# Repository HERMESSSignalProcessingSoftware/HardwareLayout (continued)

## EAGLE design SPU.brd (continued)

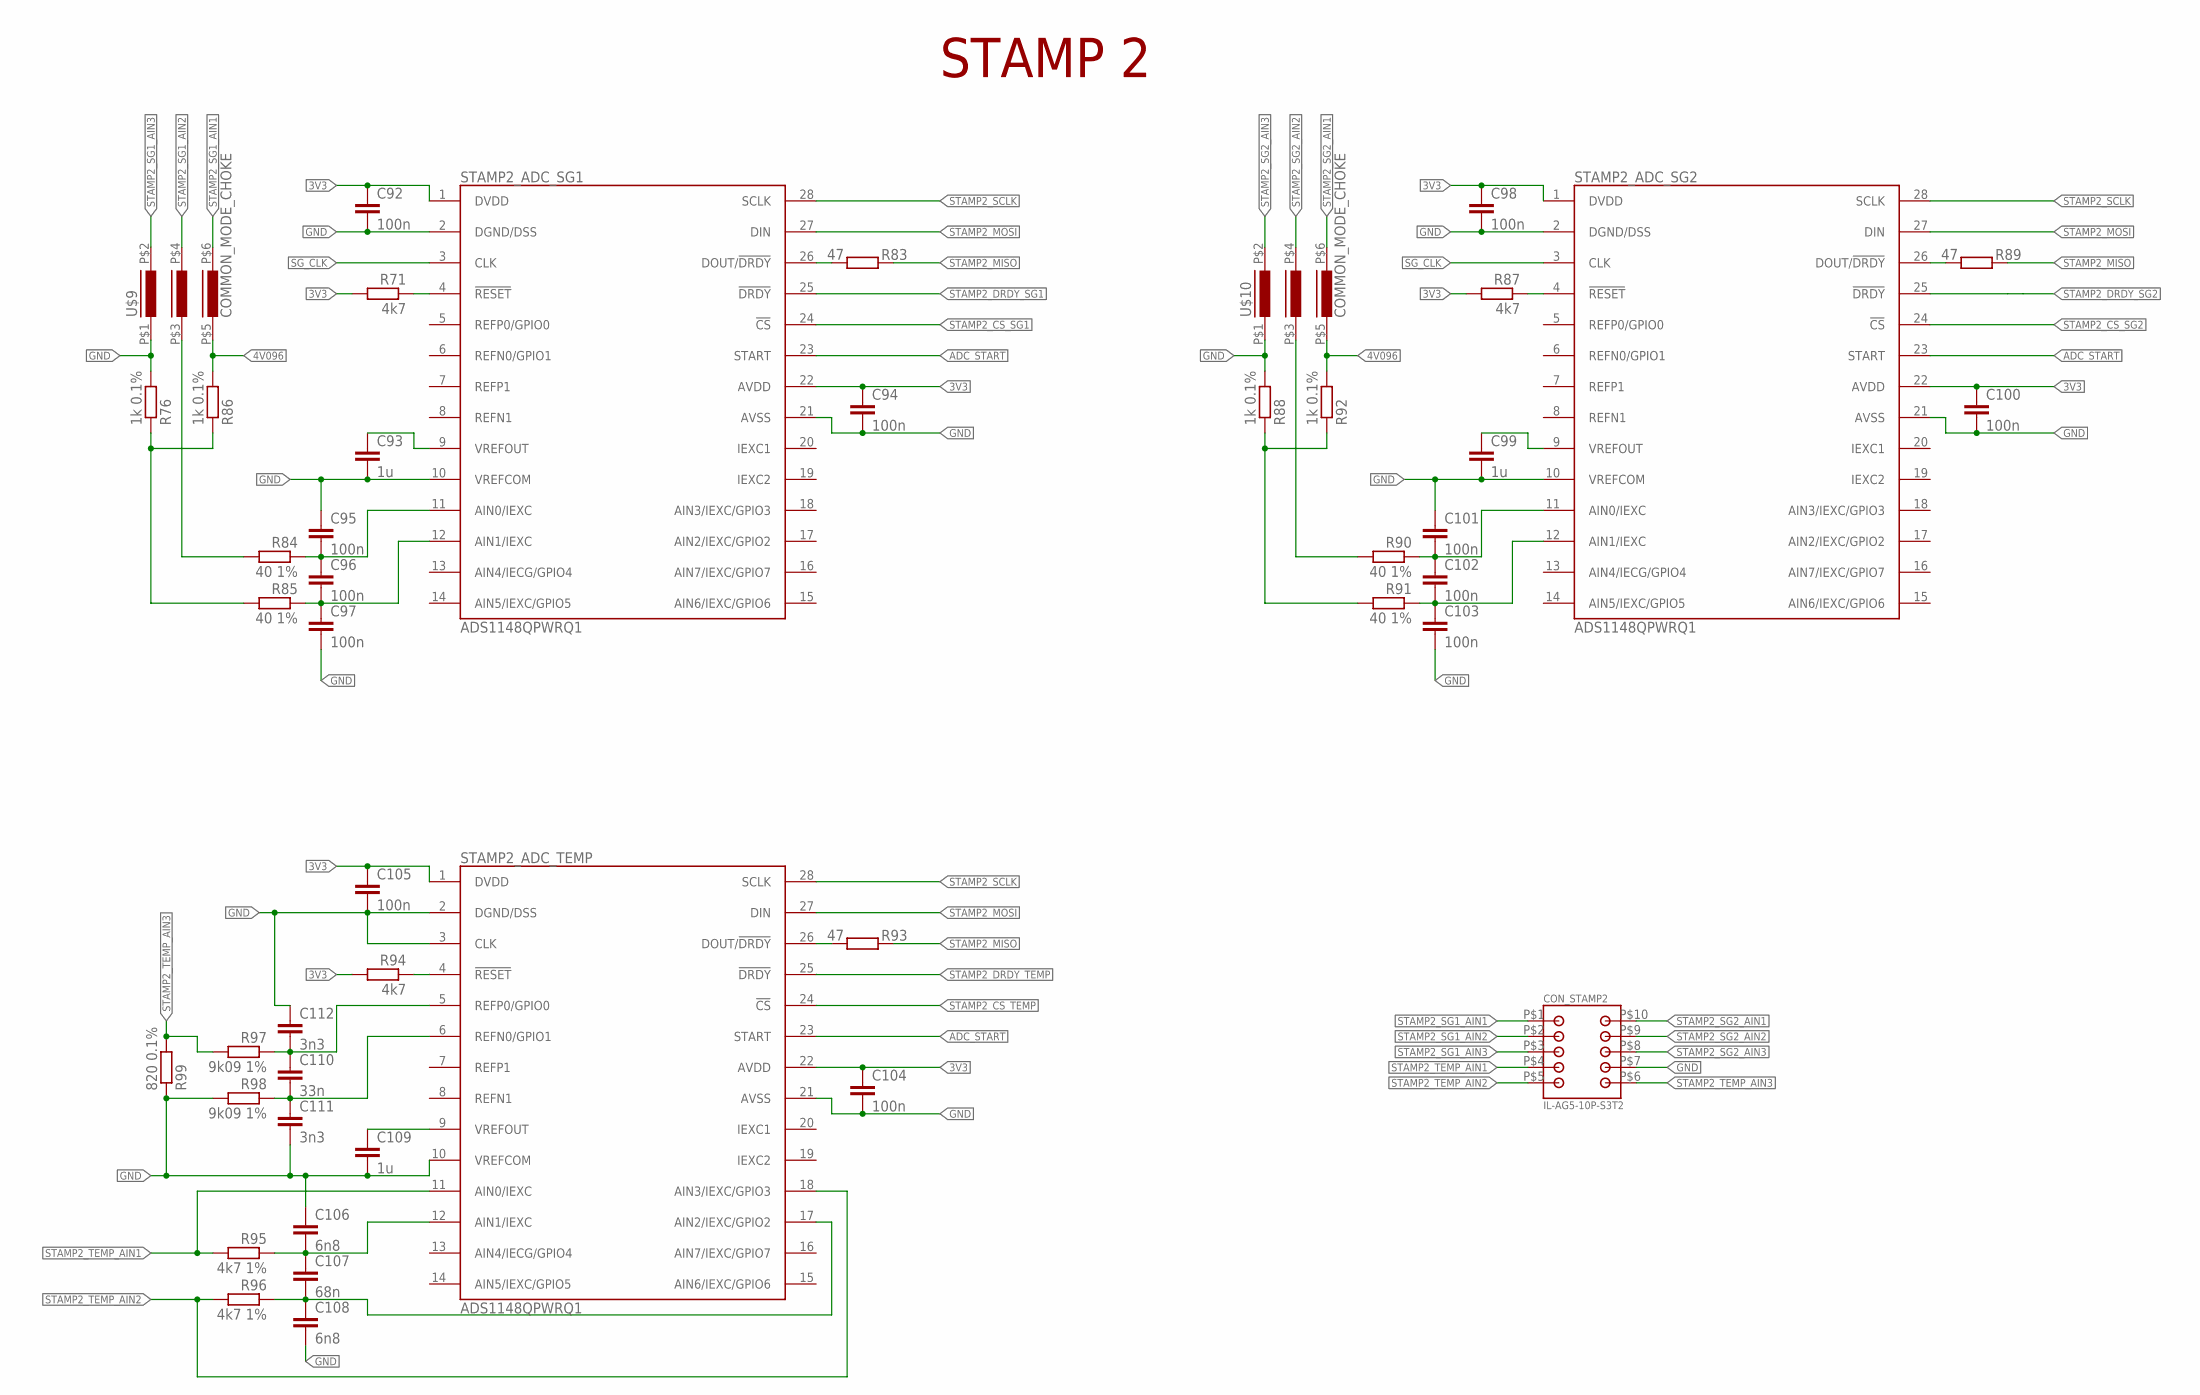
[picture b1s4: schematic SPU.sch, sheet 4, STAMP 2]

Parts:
C92, C94, C95, C96, C97, C98, C100, C101, C102, C103, C104, C105: 100n; C0805
C93, C99, C109: 1u; C0805
C106, C108: 6n8; C0805
C107: 68n; C0805
C110: 33n; C0805
C111, C112: 3n3; C0805
CON_STAMP2: IL-AG5-10P-S3T2
R71, R87, R94: 4k7; R0805
R76, R86, R88, R92: 1k 0.1%; R0805
R83, R89, R93: 47; R0805
R84, R85, R90, R91: 40 1%; R0805
R95, R96: 4k7 1%; R0805
R97, R98: 9k09 1%; R0805
R99: 820 0.1%; R0805
STAMP2_ADC_SG1, STAMP2_ADC_SG2, STAMP2_ADC_TEMP: ADS1148QPWRQ1; TSSOP28
U$9, U$10: COMMON_MODE_CHOKE

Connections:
3V3: C92.1, C94.1, C98.1, C100.1, C104.1, C105.1, R71.2, R87.2, R94.2, STAMP2_ADC_SG1.1 (DVDD), STAMP2_ADC_SG1.22 (AVDD), STAMP2_ADC_SG2.1 (DVDD), STAMP2_ADC_SG2.22 (AVDD), STAMP2_ADC_TEMP.1 (DVDD), STAMP2_ADC_TEMP.22 (AVDD); also elsewhere on the board
4V096: R86.2, R92.2, U$9.P$5 (5), U$10.P$5 (5); also elsewhere on the board
ADC_START: STAMP2_ADC_SG1.23 (START), STAMP2_ADC_SG2.23 (START), STAMP2_ADC_TEMP.23 (START); also elsewhere on the board
GND: C92.2, C93.2, C94.2, C95.1, C97.2, C98.2, C99.2, C100.2, C101.1, C103.2, C104.2, C105.2, C106.1, C108.2, C109.2, C111.2, C112.1, CON_STAMP2.P$7, R76.2, R88.2, R98.2, R99.1, STAMP2_ADC_SG1.2 (DGND/DSS), STAMP2_ADC_SG1.10 (VREFCOM), STAMP2_ADC_SG1.21 (AVSS), STAMP2_ADC_SG2.2 (DGND/DSS), STAMP2_ADC_SG2.10 (VREFCOM), STAMP2_ADC_SG2.21 (AVSS), STAMP2_ADC_TEMP.2 (DGND/DSS), STAMP2_ADC_TEMP.3 (CLK), STAMP2_ADC_TEMP.10 (VREFCOM), STAMP2_ADC_TEMP.21 (AVSS), U$9.P$1 (1), U$10.P$1 (1); also elsewhere on the board
unnamed: R71.1, STAMP2_ADC_SG1.4 (!RESET)
unnamed: C93.1, STAMP2_ADC_SG1.9 (VREFOUT)
unnamed: R83.2, STAMP2_ADC_SG1.26 (DOUT/!DRDY)
unnamed: C95.2, C96.1, R84.1, STAMP2_ADC_SG1.11 (AIN0/IEXC)
unnamed: C96.2, C97.1, R85.1, STAMP2_ADC_SG1.12 (AIN1/IEXC)
unnamed: R76.1, R85.2, R86.1
unnamed: R84.2, U$9.P$3 (3)
unnamed: R87.1, STAMP2_ADC_SG2.4 (!RESET)
unnamed: C99.1, STAMP2_ADC_SG2.9 (VREFOUT)
unnamed: R89.2, STAMP2_ADC_SG2.26 (DOUT/!DRDY)
unnamed: C101.2, C102.1, R90.1, STAMP2_ADC_SG2.11 (AIN0/IEXC)
unnamed: C102.2, C103.1, R91.1, STAMP2_ADC_SG2.12 (AIN1/IEXC)
unnamed: R88.1, R91.2, R92.1
unnamed: R90.2, U$10.P$3 (3)
unnamed: R93.2, STAMP2_ADC_TEMP.26 (DOUT/!DRDY)
unnamed: R94.1, STAMP2_ADC_TEMP.4 (!RESET)
unnamed: C106.2, C107.1, R95.1, STAMP2_ADC_TEMP.12 (AIN1/IEXC)
unnamed: C107.2, C108.1, R96.1, STAMP2_ADC_TEMP.17 (AIN2/IEXC/GPIO2)
unnamed: C109.1, STAMP2_ADC_TEMP.9 (VREFOUT)
S2AT1: C110.1, C112.2, R97.1, STAMP2_ADC_TEMP.5 (REFP0/GPIO0)
S2AT2: C110.2, C111.1, R98.1, STAMP2_ADC_TEMP.6 (REFN0/GPIO1)
SG_CLK: STAMP2_ADC_SG1.3 (CLK), STAMP2_ADC_SG2.3 (CLK); also elsewhere on the board
STAMP2_CS_SG1: STAMP2_ADC_SG1.24 (!CS); also elsewhere on the board
STAMP2_CS_SG2: STAMP2_ADC_SG2.24 (!CS); also elsewhere on the board
STAMP2_CS_TEMP: STAMP2_ADC_TEMP.24 (!CS); also elsewhere on the board
STAMP2_DRDY_SG1: STAMP2_ADC_SG1.25 (!DRDY); also elsewhere on the board
STAMP2_DRDY_SG2: STAMP2_ADC_SG2.25 (!DRDY); also elsewhere on the board
STAMP2_DRDY_TEMP: STAMP2_ADC_TEMP.25 (!DRDY); also elsewhere on the board
STAMP2_MISO: R83.1, R89.1, R93.1; also elsewhere on the board
STAMP2_MOSI: STAMP2_ADC_SG1.27 (DIN), STAMP2_ADC_SG2.27 (DIN), STAMP2_ADC_TEMP.27 (DIN); also elsewhere on the board
STAMP2_SCLK: STAMP2_ADC_SG1.28 (SCLK), STAMP2_ADC_SG2.28 (SCLK), STAMP2_ADC_TEMP.28 (SCLK); also elsewhere on the board
STAMP2_SG1_AIN1: CON_STAMP2.P$1, U$9.P$6 (6)
STAMP2_SG1_AIN2: CON_STAMP2.P$2, U$9.P$4 (4)
STAMP2_SG1_AIN3: CON_STAMP2.P$3, U$9.P$2 (2)
STAMP2_SG2_AIN1: CON_STAMP2.P$10, U$10.P$6 (6)
STAMP2_SG2_AIN2: CON_STAMP2.P$9, U$10.P$4 (4)
STAMP2_SG2_AIN3: CON_STAMP2.P$8, U$10.P$2 (2)
STAMP2_TEMP_AIN1: CON_STAMP2.P$4, R95.2, STAMP2_ADC_TEMP.11 (AIN0/IEXC)
STAMP2_TEMP_AIN2: CON_STAMP2.P$5, R96.2, STAMP2_ADC_TEMP.18 (AIN3/IEXC/GPIO3)
STAMP2_TEMP_AIN3: CON_STAMP2.P$6, R97.2, R99.2

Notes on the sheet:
STAMP 2

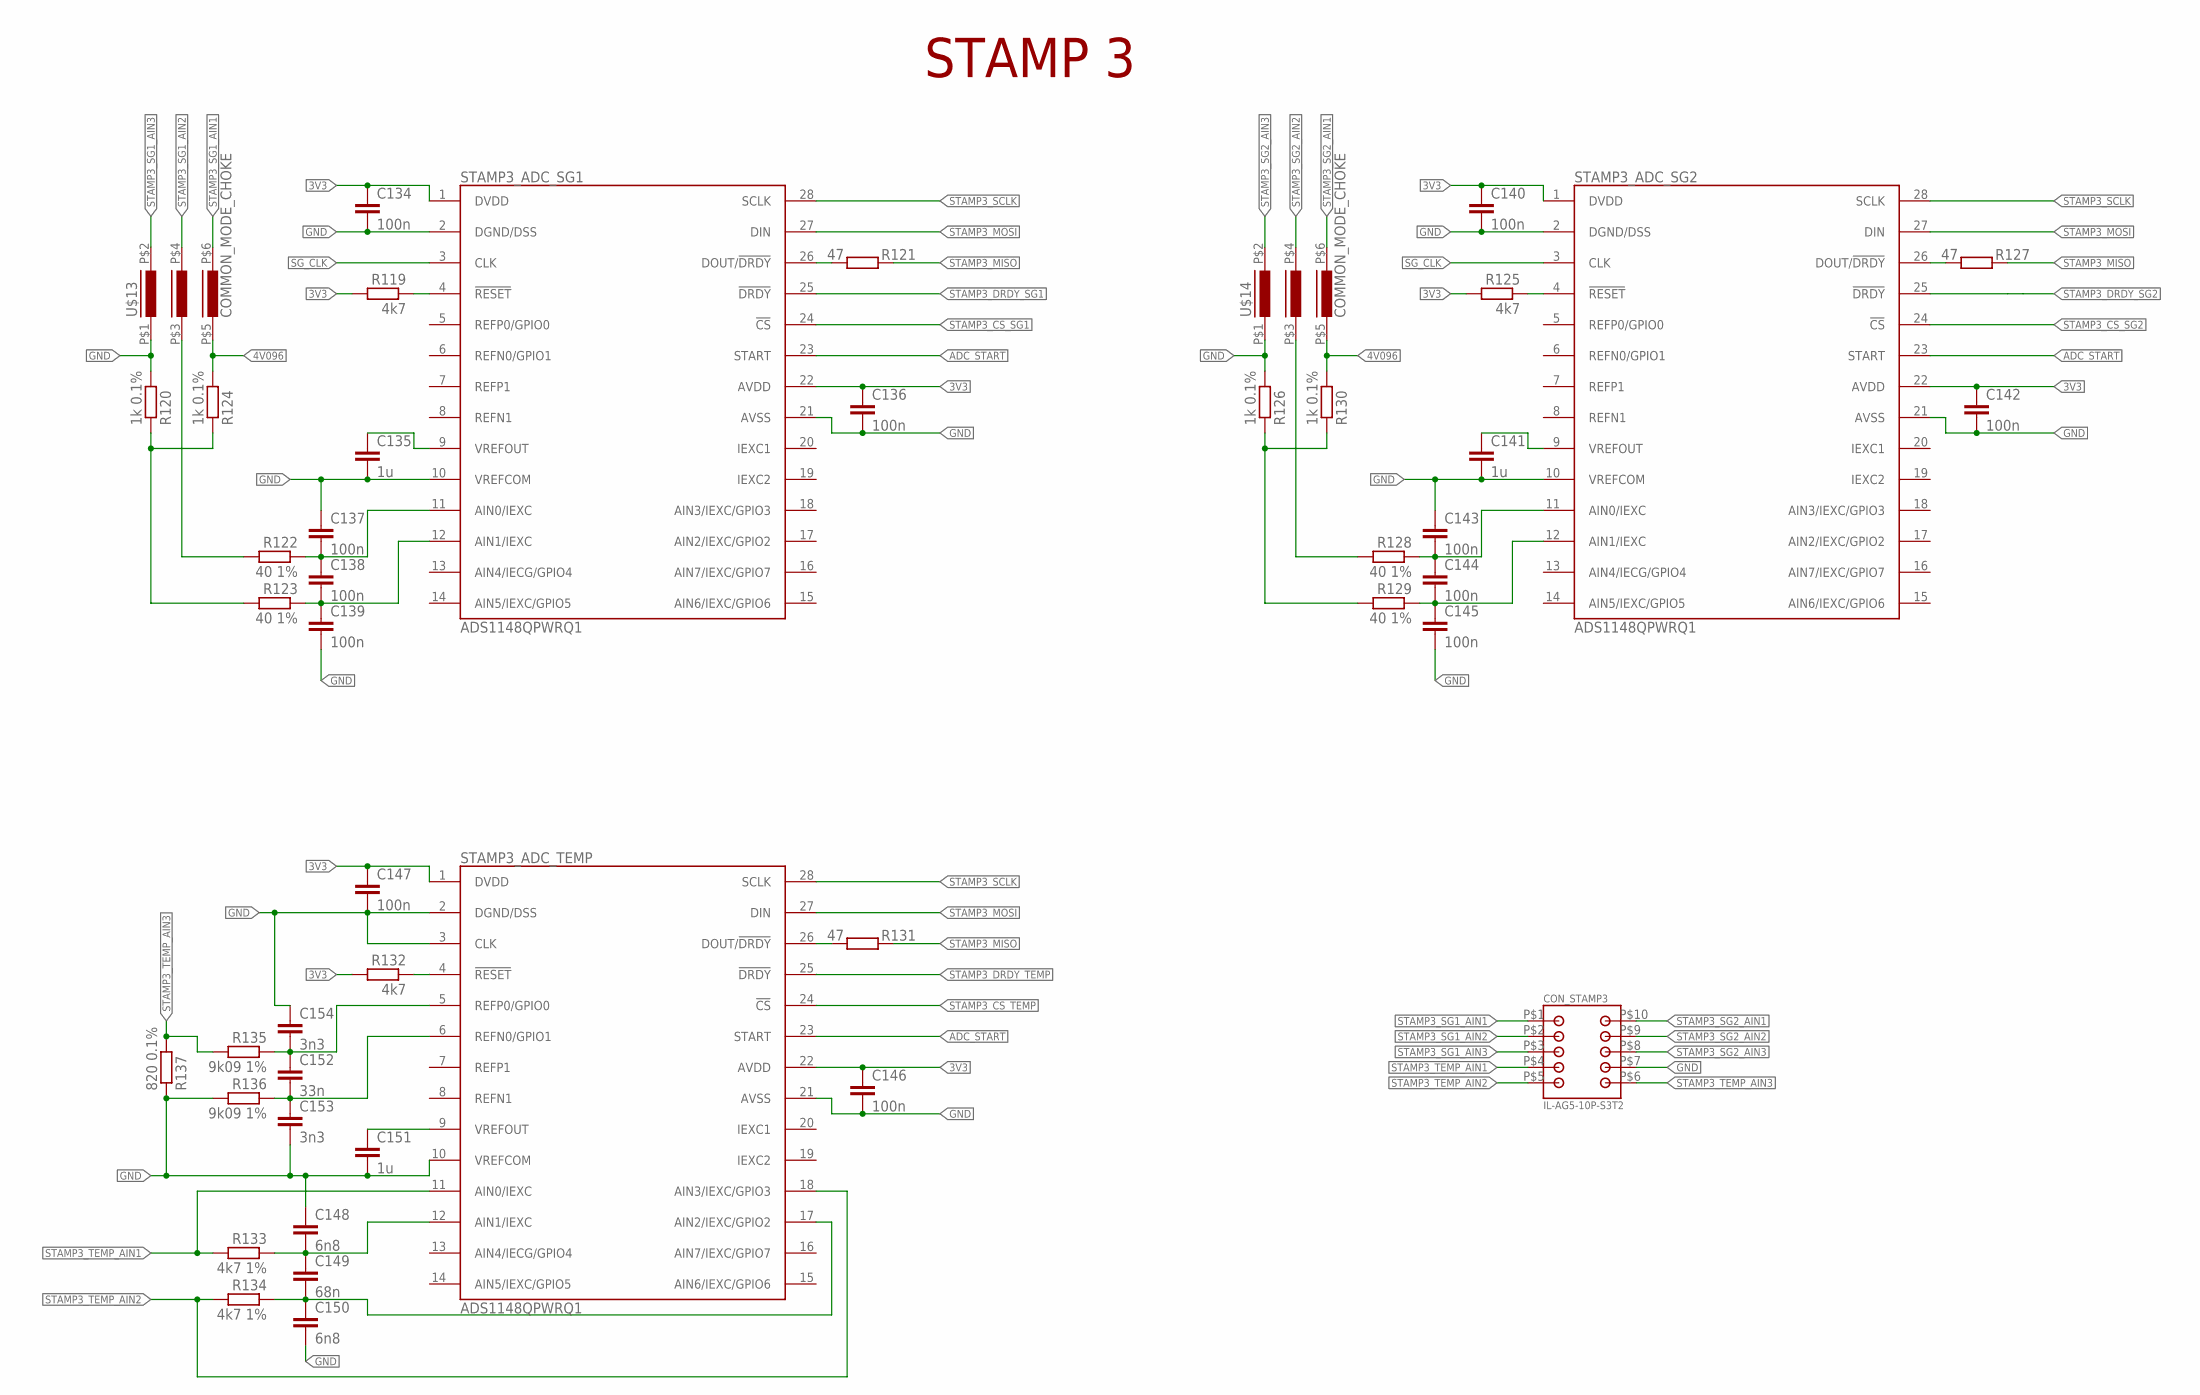
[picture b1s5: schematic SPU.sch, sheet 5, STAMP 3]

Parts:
C134, C136, C137, C138, C139, C140, C142, C143, C144, C145, C146, C147: 100n; C0805
C135, C141, C151: 1u; C0805
C148, C150: 6n8; C0805
C149: 68n; C0805
C152: 33n; C0805
C153, C154: 3n3; C0805
CON_STAMP3: IL-AG5-10P-S3T2
R119, R125, R132: 4k7; R0805
R120, R124, R126, R130: 1k 0.1%; R0805
R121, R127, R131: 47; R0805
R122, R123, R128, R129: 40 1%; R0805
R133, R134: 4k7 1%; R0805
R135, R136: 9k09 1%; R0805
R137: 820 0.1%; R0805
STAMP3_ADC_SG1, STAMP3_ADC_SG2, STAMP3_ADC_TEMP: ADS1148QPWRQ1; TSSOP28
U$13, U$14: COMMON_MODE_CHOKE

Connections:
3V3: C134.1, C136.1, C140.1, C142.1, C146.1, C147.1, R119.2, R125.2, R132.2, STAMP3_ADC_SG1.1 (DVDD), STAMP3_ADC_SG1.22 (AVDD), STAMP3_ADC_SG2.1 (DVDD), STAMP3_ADC_SG2.22 (AVDD), STAMP3_ADC_TEMP.1 (DVDD), STAMP3_ADC_TEMP.22 (AVDD); also elsewhere on the board
4V096: R124.2, R130.2, U$13.P$5 (5), U$14.P$5 (5); also elsewhere on the board
ADC_START: STAMP3_ADC_SG1.23 (START), STAMP3_ADC_SG2.23 (START), STAMP3_ADC_TEMP.23 (START); also elsewhere on the board
GND: C134.2, C135.2, C136.2, C137.1, C139.2, C140.2, C141.2, C142.2, C143.1, C145.2, C146.2, C147.2, C148.1, C150.2, C151.2, C153.2, C154.1, CON_STAMP3.P$7, R120.2, R126.2, R136.2, R137.1, STAMP3_ADC_SG1.2 (DGND/DSS), STAMP3_ADC_SG1.10 (VREFCOM), STAMP3_ADC_SG1.21 (AVSS), STAMP3_ADC_SG2.2 (DGND/DSS), STAMP3_ADC_SG2.10 (VREFCOM), STAMP3_ADC_SG2.21 (AVSS), STAMP3_ADC_TEMP.2 (DGND/DSS), STAMP3_ADC_TEMP.3 (CLK), STAMP3_ADC_TEMP.10 (VREFCOM), STAMP3_ADC_TEMP.21 (AVSS), U$13.P$1 (1), U$14.P$1 (1); also elsewhere on the board
unnamed: R119.1, STAMP3_ADC_SG1.4 (!RESET)
unnamed: C135.1, STAMP3_ADC_SG1.9 (VREFOUT)
unnamed: R121.2, STAMP3_ADC_SG1.26 (DOUT/!DRDY)
unnamed: C137.2, C138.1, R122.1, STAMP3_ADC_SG1.11 (AIN0/IEXC)
unnamed: C138.2, C139.1, R123.1, STAMP3_ADC_SG1.12 (AIN1/IEXC)
unnamed: R120.1, R123.2, R124.1
unnamed: R122.2, U$13.P$3 (3)
unnamed: R125.1, STAMP3_ADC_SG2.4 (!RESET)
unnamed: C141.1, STAMP3_ADC_SG2.9 (VREFOUT)
unnamed: R127.2, STAMP3_ADC_SG2.26 (DOUT/!DRDY)
unnamed: C143.2, C144.1, R128.1, STAMP3_ADC_SG2.11 (AIN0/IEXC)
unnamed: C144.2, C145.1, R129.1, STAMP3_ADC_SG2.12 (AIN1/IEXC)
unnamed: R126.1, R129.2, R130.1
unnamed: R128.2, U$14.P$3 (3)
unnamed: R131.2, STAMP3_ADC_TEMP.26 (DOUT/!DRDY)
unnamed: R132.1, STAMP3_ADC_TEMP.4 (!RESET)
unnamed: C148.2, C149.1, R133.1, STAMP3_ADC_TEMP.12 (AIN1/IEXC)
unnamed: C149.2, C150.1, R134.1, STAMP3_ADC_TEMP.17 (AIN2/IEXC/GPIO2)
unnamed: C151.1, STAMP3_ADC_TEMP.9 (VREFOUT)
unnamed: C152.2, C153.1, R136.1, STAMP3_ADC_TEMP.6 (REFN0/GPIO1)
unnamed: C152.1, C154.2, R135.1, STAMP3_ADC_TEMP.5 (REFP0/GPIO0)
SG_CLK: STAMP3_ADC_SG1.3 (CLK), STAMP3_ADC_SG2.3 (CLK); also elsewhere on the board
STAMP3_CS_SG1: STAMP3_ADC_SG1.24 (!CS); also elsewhere on the board
STAMP3_CS_SG2: STAMP3_ADC_SG2.24 (!CS); also elsewhere on the board
STAMP3_CS_TEMP: STAMP3_ADC_TEMP.24 (!CS); also elsewhere on the board
STAMP3_DRDY_SG1: STAMP3_ADC_SG1.25 (!DRDY); also elsewhere on the board
STAMP3_DRDY_SG2: STAMP3_ADC_SG2.25 (!DRDY); also elsewhere on the board
STAMP3_DRDY_TEMP: STAMP3_ADC_TEMP.25 (!DRDY); also elsewhere on the board
STAMP3_MISO: R121.1, R127.1, R131.1; also elsewhere on the board
STAMP3_MOSI: STAMP3_ADC_SG1.27 (DIN), STAMP3_ADC_SG2.27 (DIN), STAMP3_ADC_TEMP.27 (DIN); also elsewhere on the board
STAMP3_SCLK: STAMP3_ADC_SG1.28 (SCLK), STAMP3_ADC_SG2.28 (SCLK), STAMP3_ADC_TEMP.28 (SCLK); also elsewhere on the board
STAMP3_SG1_AIN1: CON_STAMP3.P$1, U$13.P$6 (6)
STAMP3_SG1_AIN2: CON_STAMP3.P$2, U$13.P$4 (4)
STAMP3_SG1_AIN3: CON_STAMP3.P$3, U$13.P$2 (2)
STAMP3_SG2_AIN1: CON_STAMP3.P$10, U$14.P$6 (6)
STAMP3_SG2_AIN2: CON_STAMP3.P$9, U$14.P$4 (4)
STAMP3_SG2_AIN3: CON_STAMP3.P$8, U$14.P$2 (2)
STAMP3_TEMP_AIN1: CON_STAMP3.P$4, R133.2, STAMP3_ADC_TEMP.11 (AIN0/IEXC)
STAMP3_TEMP_AIN2: CON_STAMP3.P$5, R134.2, STAMP3_ADC_TEMP.18 (AIN3/IEXC/GPIO3)
STAMP3_TEMP_AIN3: CON_STAMP3.P$6, R135.2, R137.2

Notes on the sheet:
STAMP 3

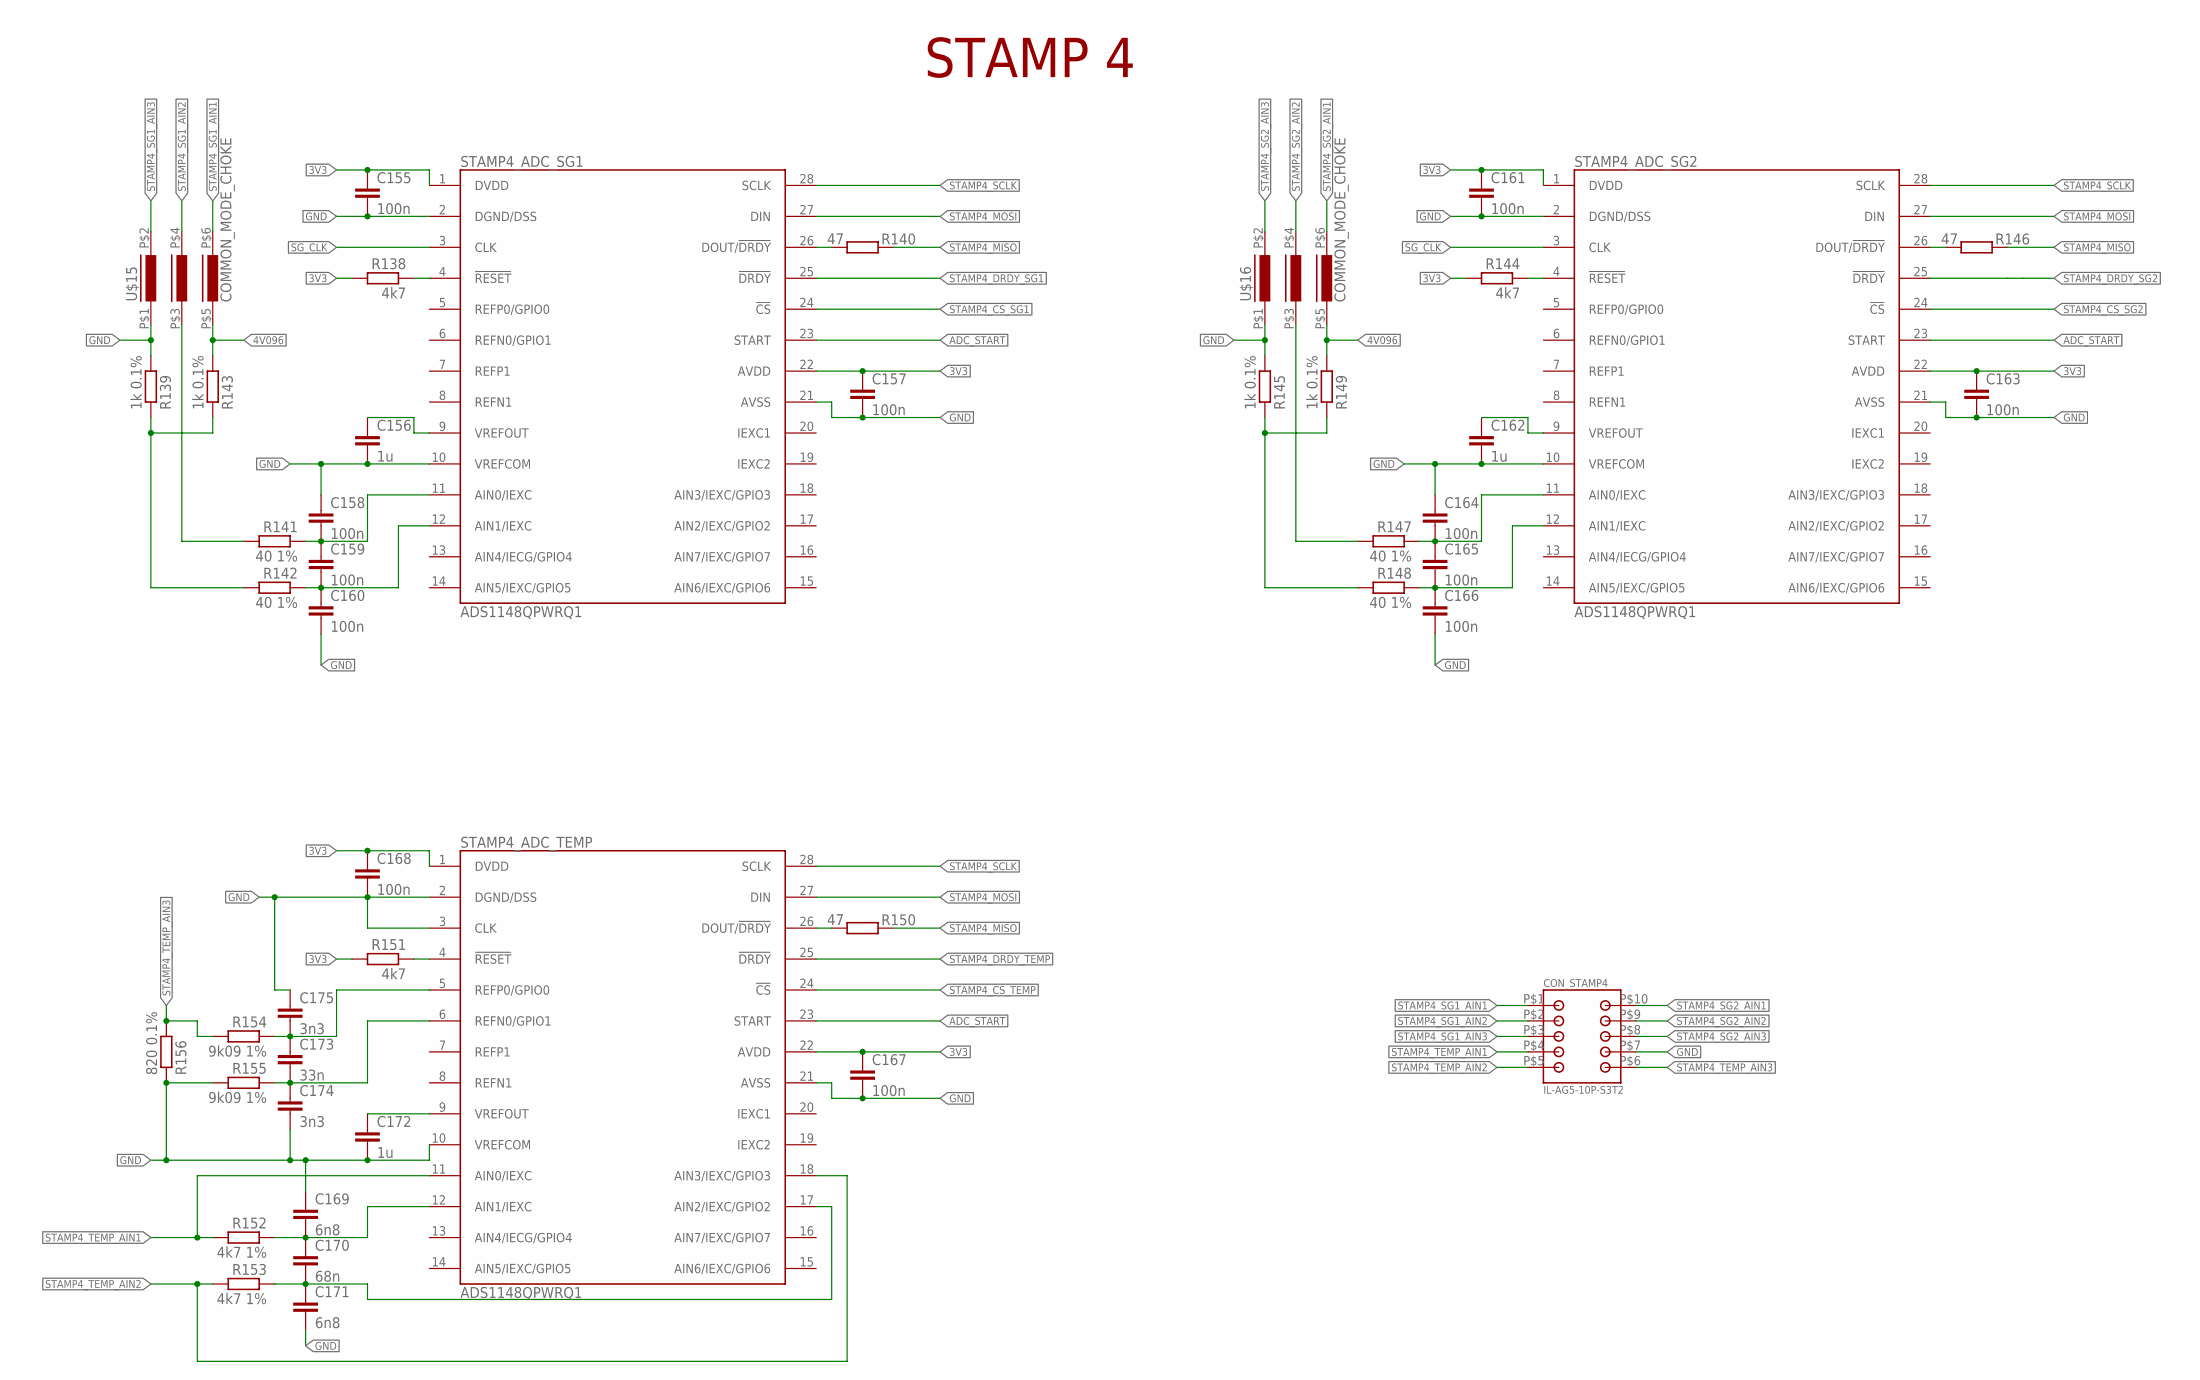
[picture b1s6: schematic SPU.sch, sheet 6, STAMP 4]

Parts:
C155, C157, C158, C159, C160, C161, C163, C164, C165, C166, C167, C168: 100n; C0805
C156, C162, C172: 1u; C0805
C169, C171: 6n8; C0805
C170: 68n; C0805
C173: 33n; C0805
C174, C175: 3n3; C0805
CON_STAMP4: IL-AG5-10P-S3T2
R138, R144, R151: 4k7; R0805
R139, R143, R145, R149: 1k 0.1%; R0805
R140, R146, R150: 47; R0805
R141, R142, R147, R148: 40 1%; R0805
R152, R153: 4k7 1%; R0805
R154, R155: 9k09 1%; R0805
R156: 820 0.1%; R0805
STAMP4_ADC_SG1, STAMP4_ADC_SG2, STAMP4_ADC_TEMP: ADS1148QPWRQ1; TSSOP28
U$15, U$16: COMMON_MODE_CHOKE

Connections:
3V3: C155.1, C157.1, C161.1, C163.1, C167.1, C168.1, R138.2, R144.2, R151.2, STAMP4_ADC_SG1.1 (DVDD), STAMP4_ADC_SG1.22 (AVDD), STAMP4_ADC_SG2.1 (DVDD), STAMP4_ADC_SG2.22 (AVDD), STAMP4_ADC_TEMP.1 (DVDD), STAMP4_ADC_TEMP.22 (AVDD); also elsewhere on the board
4V096: R143.2, R149.2, U$15.P$5 (5), U$16.P$5 (5); also elsewhere on the board
ADC_START: STAMP4_ADC_SG1.23 (START), STAMP4_ADC_SG2.23 (START), STAMP4_ADC_TEMP.23 (START); also elsewhere on the board
GND: C155.2, C156.2, C157.2, C158.1, C160.2, C161.2, C162.2, C163.2, C164.1, C166.2, C167.2, C168.2, C169.1, C171.2, C172.2, C174.2, C175.1, CON_STAMP4.P$7, R139.2, R145.2, R155.2, R156.1, STAMP4_ADC_SG1.2 (DGND/DSS), STAMP4_ADC_SG1.10 (VREFCOM), STAMP4_ADC_SG1.21 (AVSS), STAMP4_ADC_SG2.2 (DGND/DSS), STAMP4_ADC_SG2.10 (VREFCOM), STAMP4_ADC_SG2.21 (AVSS), STAMP4_ADC_TEMP.2 (DGND/DSS), STAMP4_ADC_TEMP.3 (CLK), STAMP4_ADC_TEMP.10 (VREFCOM), STAMP4_ADC_TEMP.21 (AVSS), U$15.P$1 (1), U$16.P$1 (1); also elsewhere on the board
unnamed: R138.1, STAMP4_ADC_SG1.4 (!RESET)
unnamed: C156.1, STAMP4_ADC_SG1.9 (VREFOUT)
unnamed: R140.2, STAMP4_ADC_SG1.26 (DOUT/!DRDY)
unnamed: C158.2, C159.1, R141.1, STAMP4_ADC_SG1.11 (AIN0/IEXC)
unnamed: C159.2, C160.1, R142.1, STAMP4_ADC_SG1.12 (AIN1/IEXC)
unnamed: R139.1, R142.2, R143.1
unnamed: R141.2, U$15.P$3 (3)
unnamed: R144.1, STAMP4_ADC_SG2.4 (!RESET)
unnamed: C162.1, STAMP4_ADC_SG2.9 (VREFOUT)
unnamed: R146.2, STAMP4_ADC_SG2.26 (DOUT/!DRDY)
unnamed: C164.2, C165.1, R147.1, STAMP4_ADC_SG2.11 (AIN0/IEXC)
unnamed: C165.2, C166.1, R148.1, STAMP4_ADC_SG2.12 (AIN1/IEXC)
unnamed: R145.1, R148.2, R149.1
unnamed: R147.2, U$16.P$3 (3)
unnamed: R150.2, STAMP4_ADC_TEMP.26 (DOUT/!DRDY)
unnamed: R151.1, STAMP4_ADC_TEMP.4 (!RESET)
unnamed: C169.2, C170.1, R152.1, STAMP4_ADC_TEMP.12 (AIN1/IEXC)
unnamed: C170.2, C171.1, R153.1, STAMP4_ADC_TEMP.17 (AIN2/IEXC/GPIO2)
unnamed: C172.1, STAMP4_ADC_TEMP.9 (VREFOUT)
unnamed: C173.2, C174.1, R155.1, STAMP4_ADC_TEMP.6 (REFN0/GPIO1)
unnamed: C173.1, C175.2, R154.1, STAMP4_ADC_TEMP.5 (REFP0/GPIO0)
SG_CLK: STAMP4_ADC_SG1.3 (CLK), STAMP4_ADC_SG2.3 (CLK); also elsewhere on the board
STAMP4_CS_SG1: STAMP4_ADC_SG1.24 (!CS); also elsewhere on the board
STAMP4_CS_SG2: STAMP4_ADC_SG2.24 (!CS); also elsewhere on the board
STAMP4_CS_TEMP: STAMP4_ADC_TEMP.24 (!CS); also elsewhere on the board
STAMP4_DRDY_SG1: STAMP4_ADC_SG1.25 (!DRDY); also elsewhere on the board
STAMP4_DRDY_SG2: STAMP4_ADC_SG2.25 (!DRDY); also elsewhere on the board
STAMP4_DRDY_TEMP: STAMP4_ADC_TEMP.25 (!DRDY); also elsewhere on the board
STAMP4_MISO: R140.1, R146.1, R150.1; also elsewhere on the board
STAMP4_MOSI: STAMP4_ADC_SG1.27 (DIN), STAMP4_ADC_SG2.27 (DIN), STAMP4_ADC_TEMP.27 (DIN); also elsewhere on the board
STAMP4_SCLK: STAMP4_ADC_SG1.28 (SCLK), STAMP4_ADC_SG2.28 (SCLK), STAMP4_ADC_TEMP.28 (SCLK); also elsewhere on the board
STAMP4_SG1_AIN1: CON_STAMP4.P$1, U$15.P$6 (6)
STAMP4_SG1_AIN2: CON_STAMP4.P$2, U$15.P$4 (4)
STAMP4_SG1_AIN3: CON_STAMP4.P$3, U$15.P$2 (2)
STAMP4_SG2_AIN1: CON_STAMP4.P$10, U$16.P$6 (6)
STAMP4_SG2_AIN2: CON_STAMP4.P$9, U$16.P$4 (4)
STAMP4_SG2_AIN3: CON_STAMP4.P$8, U$16.P$2 (2)
STAMP4_TEMP_AIN1: CON_STAMP4.P$4, R152.2, STAMP4_ADC_TEMP.11 (AIN0/IEXC)
STAMP4_TEMP_AIN2: CON_STAMP4.P$5, R153.2, STAMP4_ADC_TEMP.18 (AIN3/IEXC/GPIO3)
STAMP4_TEMP_AIN3: CON_STAMP4.P$6, R154.2, R156.2

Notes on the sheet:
STAMP 4

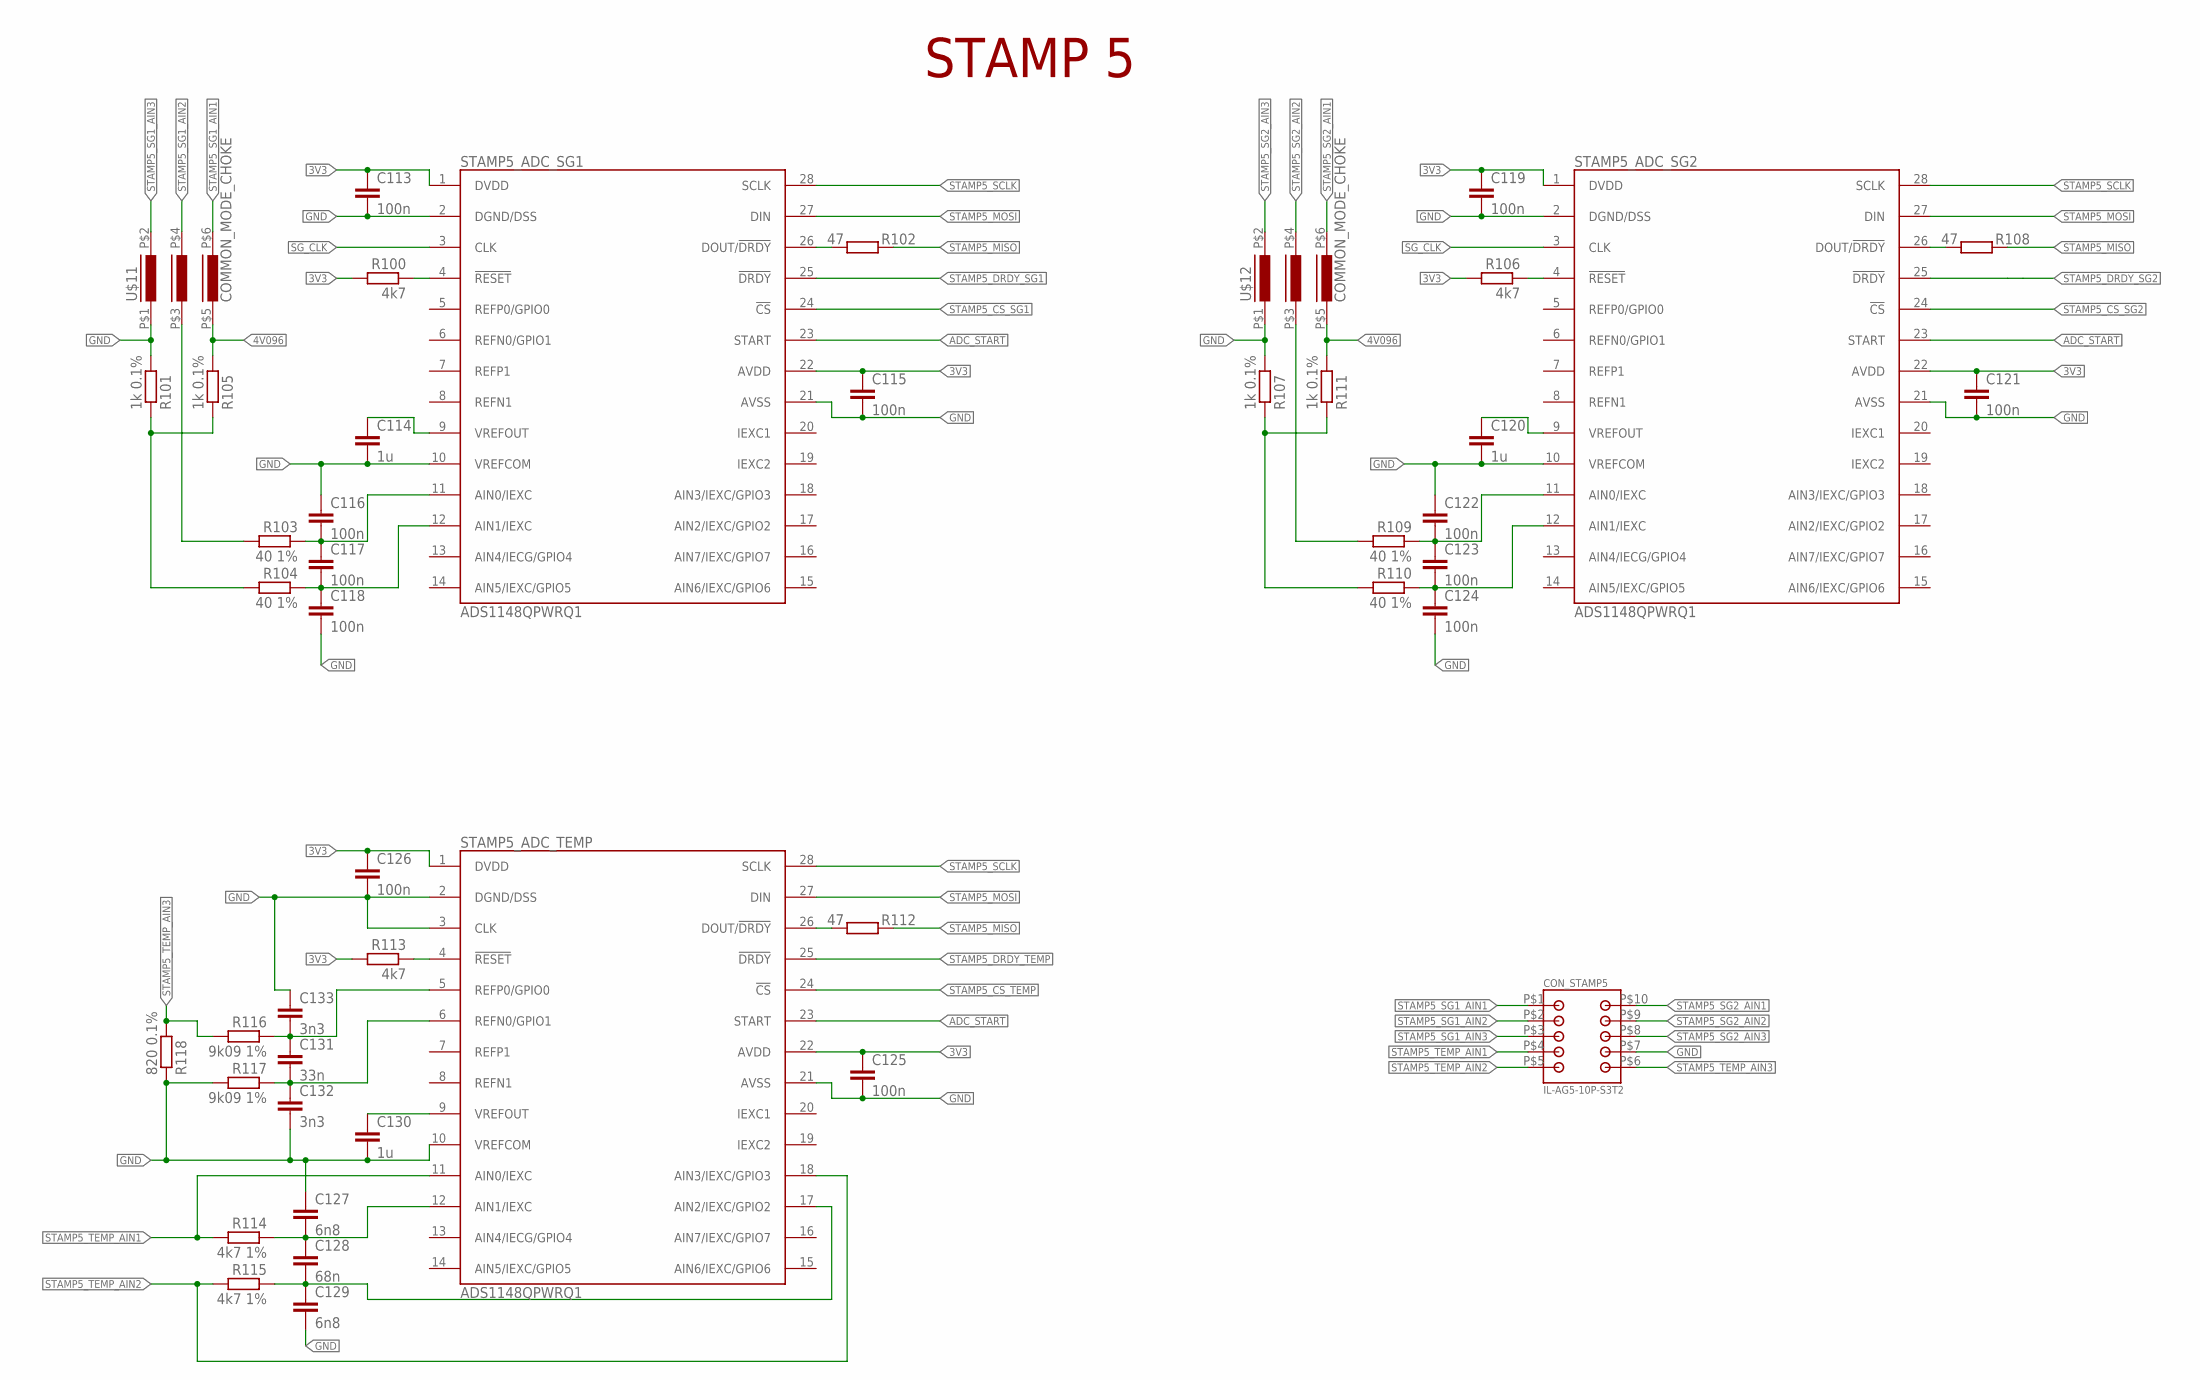
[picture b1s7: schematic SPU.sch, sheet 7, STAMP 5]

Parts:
C113, C115, C116, C117, C118, C119, C121, C122, C123, C124, C125, C126: 100n; C0805
C114, C120, C130: 1u; C0805
C127, C129: 6n8; C0805
C128: 68n; C0805
C131: 33n; C0805
C132, C133: 3n3; C0805
CON_STAMP5: IL-AG5-10P-S3T2
R100, R106, R113: 4k7; R0805
R101, R105, R107, R111: 1k 0.1%; R0805
R102, R108, R112: 47; R0805
R103, R104, R109, R110: 40 1%; R0805
R114, R115: 4k7 1%; R0805
R116, R117: 9k09 1%; R0805
R118: 820 0.1%; R0805
STAMP5_ADC_SG1, STAMP5_ADC_SG2, STAMP5_ADC_TEMP: ADS1148QPWRQ1; TSSOP28
U$11, U$12: COMMON_MODE_CHOKE

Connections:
3V3: C113.1, C115.1, C119.1, C121.1, C125.1, C126.1, R100.2, R106.2, R113.2, STAMP5_ADC_SG1.1 (DVDD), STAMP5_ADC_SG1.22 (AVDD), STAMP5_ADC_SG2.1 (DVDD), STAMP5_ADC_SG2.22 (AVDD), STAMP5_ADC_TEMP.1 (DVDD), STAMP5_ADC_TEMP.22 (AVDD); also elsewhere on the board
4V096: R105.2, R111.2, U$11.P$5 (5), U$12.P$5 (5); also elsewhere on the board
ADC_START: STAMP5_ADC_SG1.23 (START), STAMP5_ADC_SG2.23 (START), STAMP5_ADC_TEMP.23 (START); also elsewhere on the board
GND: C113.2, C114.2, C115.2, C116.1, C118.2, C119.2, C120.2, C121.2, C122.1, C124.2, C125.2, C126.2, C127.1, C129.2, C130.2, C132.2, C133.1, CON_STAMP5.P$7, R101.2, R107.2, R117.2, R118.1, STAMP5_ADC_SG1.2 (DGND/DSS), STAMP5_ADC_SG1.10 (VREFCOM), STAMP5_ADC_SG1.21 (AVSS), STAMP5_ADC_SG2.2 (DGND/DSS), STAMP5_ADC_SG2.10 (VREFCOM), STAMP5_ADC_SG2.21 (AVSS), STAMP5_ADC_TEMP.2 (DGND/DSS), STAMP5_ADC_TEMP.3 (CLK), STAMP5_ADC_TEMP.10 (VREFCOM), STAMP5_ADC_TEMP.21 (AVSS), U$11.P$1 (1), U$12.P$1 (1); also elsewhere on the board
unnamed: R100.1, STAMP5_ADC_SG1.4 (!RESET)
unnamed: C114.1, STAMP5_ADC_SG1.9 (VREFOUT)
unnamed: R102.2, STAMP5_ADC_SG1.26 (DOUT/!DRDY)
unnamed: C116.2, C117.1, R103.1, STAMP5_ADC_SG1.11 (AIN0/IEXC)
unnamed: C117.2, C118.1, R104.1, STAMP5_ADC_SG1.12 (AIN1/IEXC)
unnamed: R101.1, R104.2, R105.1
unnamed: R103.2, U$11.P$3 (3)
unnamed: R106.1, STAMP5_ADC_SG2.4 (!RESET)
unnamed: C120.1, STAMP5_ADC_SG2.9 (VREFOUT)
unnamed: R108.2, STAMP5_ADC_SG2.26 (DOUT/!DRDY)
unnamed: C122.2, C123.1, R109.1, STAMP5_ADC_SG2.11 (AIN0/IEXC)
unnamed: C123.2, C124.1, R110.1, STAMP5_ADC_SG2.12 (AIN1/IEXC)
unnamed: R107.1, R110.2, R111.1
unnamed: R109.2, U$12.P$3 (3)
unnamed: R112.2, STAMP5_ADC_TEMP.26 (DOUT/!DRDY)
unnamed: R113.1, STAMP5_ADC_TEMP.4 (!RESET)
unnamed: C127.2, C128.1, R114.1, STAMP5_ADC_TEMP.12 (AIN1/IEXC)
unnamed: C128.2, C129.1, R115.1, STAMP5_ADC_TEMP.17 (AIN2/IEXC/GPIO2)
unnamed: C130.1, STAMP5_ADC_TEMP.9 (VREFOUT)
unnamed: C131.2, C132.1, R117.1, STAMP5_ADC_TEMP.6 (REFN0/GPIO1)
unnamed: C131.1, C133.2, R116.1, STAMP5_ADC_TEMP.5 (REFP0/GPIO0)
SG_CLK: STAMP5_ADC_SG1.3 (CLK), STAMP5_ADC_SG2.3 (CLK); also elsewhere on the board
STAMP5_CS_SG1: STAMP5_ADC_SG1.24 (!CS); also elsewhere on the board
STAMP5_CS_SG2: STAMP5_ADC_SG2.24 (!CS); also elsewhere on the board
STAMP5_CS_TEMP: STAMP5_ADC_TEMP.24 (!CS); also elsewhere on the board
STAMP5_DRDY_SG1: STAMP5_ADC_SG1.25 (!DRDY); also elsewhere on the board
STAMP5_DRDY_SG2: STAMP5_ADC_SG2.25 (!DRDY); also elsewhere on the board
STAMP5_DRDY_TEMP: STAMP5_ADC_TEMP.25 (!DRDY); also elsewhere on the board
STAMP5_MISO: R102.1, R108.1, R112.1; also elsewhere on the board
STAMP5_MOSI: STAMP5_ADC_SG1.27 (DIN), STAMP5_ADC_SG2.27 (DIN), STAMP5_ADC_TEMP.27 (DIN); also elsewhere on the board
STAMP5_SCLK: STAMP5_ADC_SG1.28 (SCLK), STAMP5_ADC_SG2.28 (SCLK), STAMP5_ADC_TEMP.28 (SCLK); also elsewhere on the board
STAMP5_SG1_AIN1: CON_STAMP5.P$1, U$11.P$6 (6)
STAMP5_SG1_AIN2: CON_STAMP5.P$2, U$11.P$4 (4)
STAMP5_SG1_AIN3: CON_STAMP5.P$3, U$11.P$2 (2)
STAMP5_SG2_AIN1: CON_STAMP5.P$10, U$12.P$6 (6)
STAMP5_SG2_AIN2: CON_STAMP5.P$9, U$12.P$4 (4)
STAMP5_SG2_AIN3: CON_STAMP5.P$8, U$12.P$2 (2)
STAMP5_TEMP_AIN1: CON_STAMP5.P$4, R114.2, STAMP5_ADC_TEMP.11 (AIN0/IEXC)
STAMP5_TEMP_AIN2: CON_STAMP5.P$5, R115.2, STAMP5_ADC_TEMP.18 (AIN3/IEXC/GPIO3)
STAMP5_TEMP_AIN3: CON_STAMP5.P$6, R116.2, R118.2

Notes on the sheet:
STAMP 5
